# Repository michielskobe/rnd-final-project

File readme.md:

# The Blendinator

This project was made for the `Research and Development: Embedded` course of the master in engineering technology at GroupT KUL. The Blendinator is a digital mixing desk which is able to mix an analog input together with a Bluetooth input. It also features several audio effects such as echo, equalizer, volume control, etc. The full audio pipeline is implemented in VHDL and deployed on the FPGA fabric of a Xilinx device. Bluetooth connection, pipeline control and the Graphical user interface are implemented on the SoC. Details about the implementation can be found below. 

## Extra information: 
Find the docs on [Gitlab pages](https://rnd-final-project-c5cfa9.gitlab.io/).

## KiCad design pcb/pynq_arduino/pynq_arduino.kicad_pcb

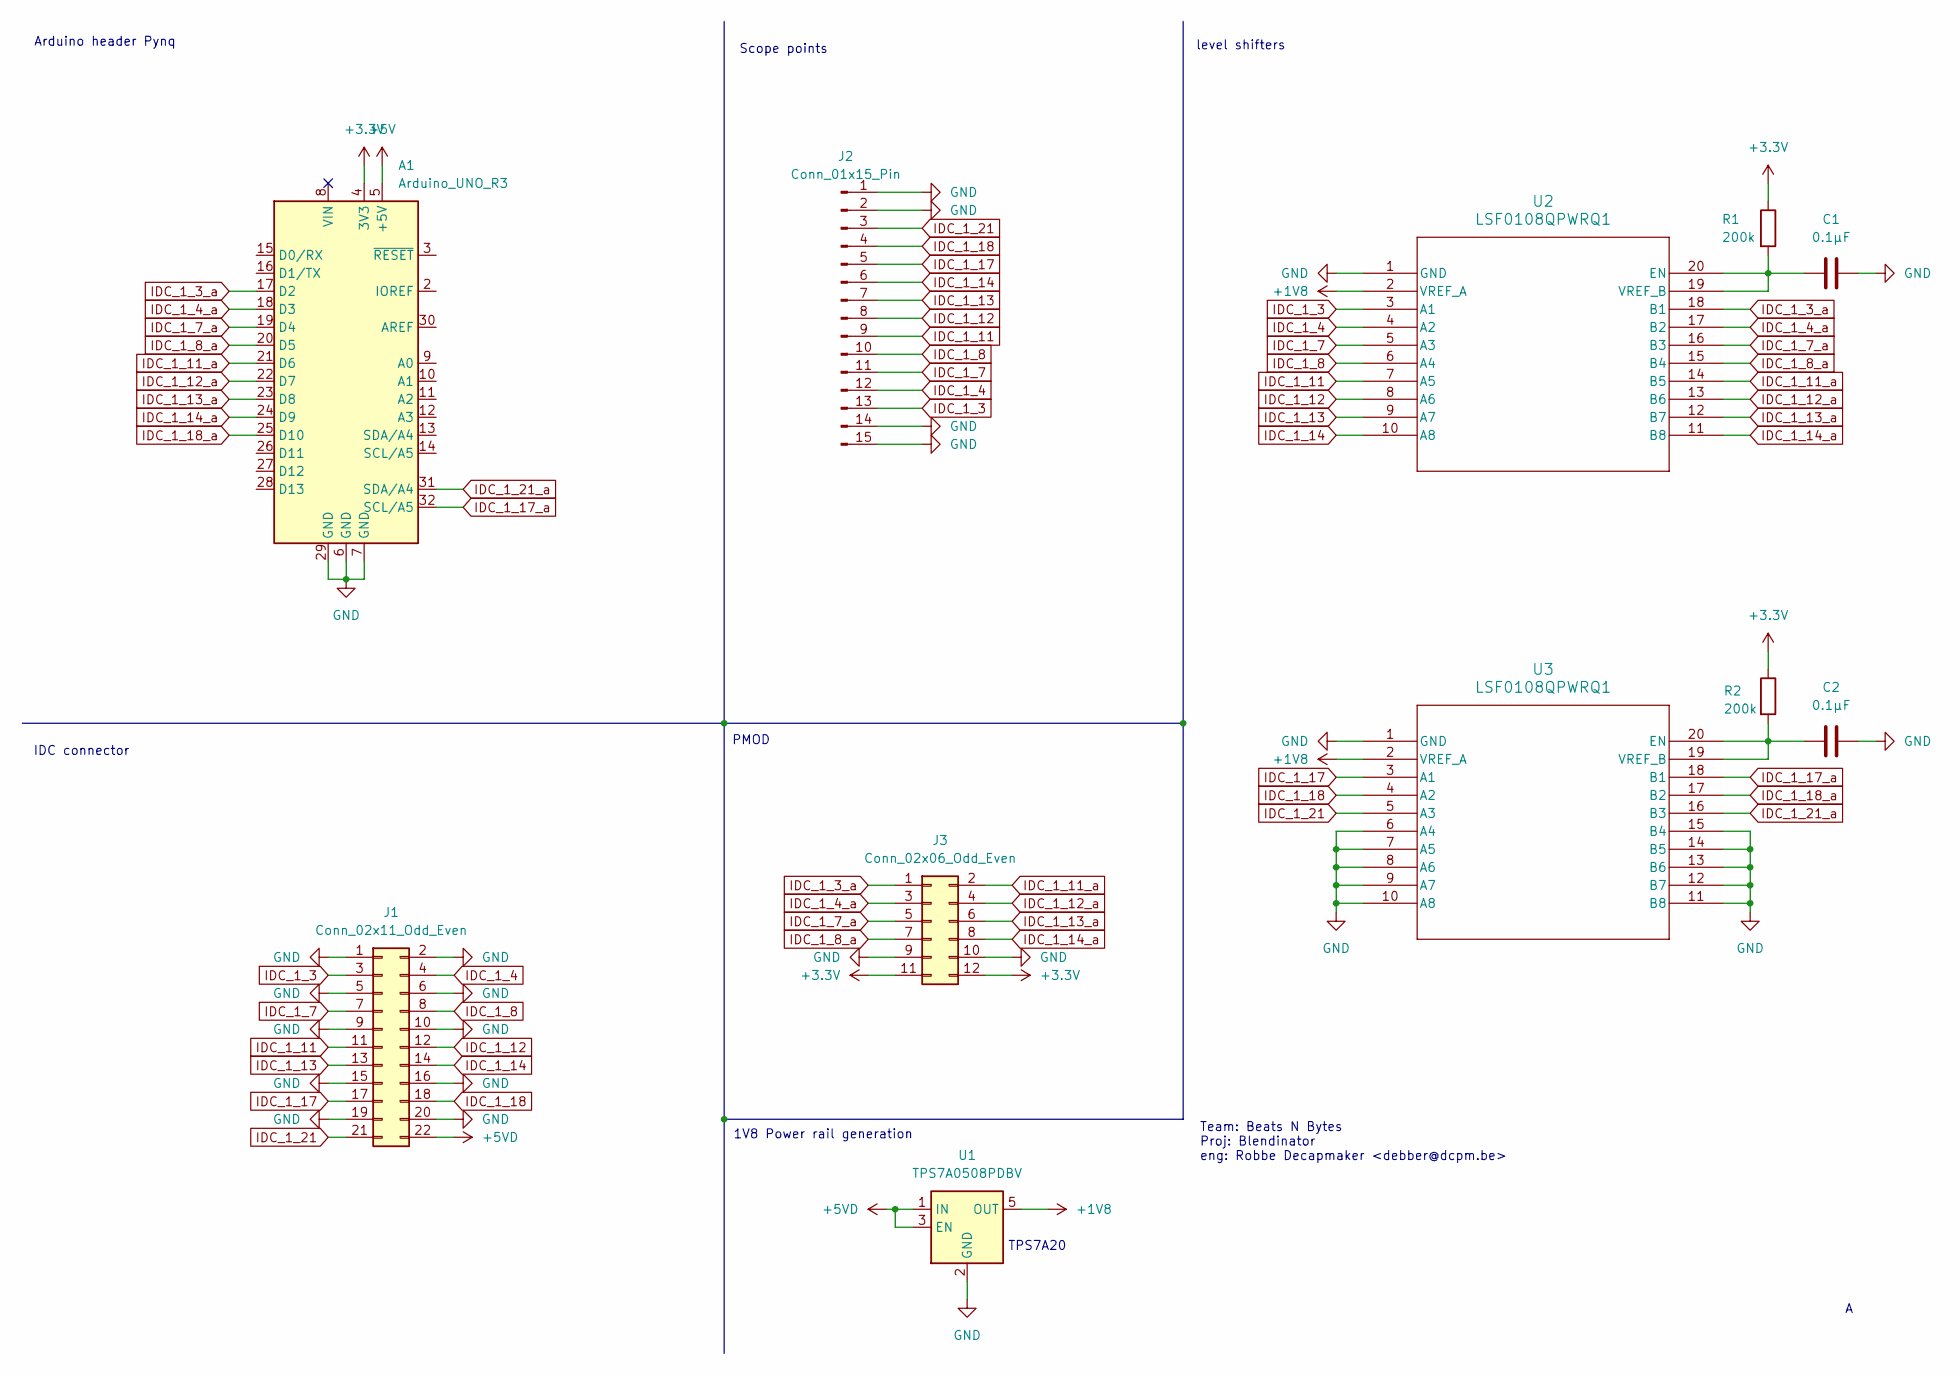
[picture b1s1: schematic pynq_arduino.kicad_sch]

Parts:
A1: Arduino_UNO_R3
C1, C2: 0.1µF; C_0805_2012Metric_Pad1.18x1.45mm_HandSolder
J1: Conn_02x11_Odd_Even; IDC-Header_2x11_P2.54mm_Vertical
J2: Conn_01x15_Pin; PinHeader_1x15_P2.54mm_Vertical
J3: Conn_02x06_Odd_Even; PinHeader_2x06_P2.54mm_Horizontal
R1, R2: 200k; R_0805_2012Metric_Pad1.20x1.40mm_HandSolder
U1: TPS7A0508PDBV; SOT-23-5
U2, U3: LSF0108QPWRQ1; PW20_TEX

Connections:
+1V8: U1.5 (OUT), U2.2 (VREF_A), U3.2 (VREF_A)
+3.3V: A1.4 (3V3), J3.11, J3.12, R1.1, R2.1
+5V: A1.5 (+5V)
+5VD: J1.22, U1.1 (IN), U1.3 (EN)
GND: A1.6 (GND), A1.7 (GND), A1.29 (GND), C1.1, C2.1, J1.1, J1.2, J1.5, J1.6, J1.9, J1.10, J1.15, J1.16, J1.19, J1.20, J2.1, J2.2, J2.14, J2.15, J3.9, J3.10, U1.2 (GND), U2.1 (GND), U3.1 (GND), U3.6 (A4), U3.7 (A5), U3.8 (A6), U3.9 (A7), U3.10 (A8), U3.11 (B8), U3.12 (B7), U3.13 (B6), U3.14 (B5), U3.15 (B4)
IDC_1_3: J1.3, J2.13, U2.3 (A1)
IDC_1_3_a: A1.17 (D2), J3.1, U2.18 (B1)
IDC_1_4: J1.4, J2.12, U2.4 (A2)
IDC_1_4_a: A1.18 (D3), J3.3, U2.17 (B2)
IDC_1_7: J1.7, J2.11, U2.5 (A3)
IDC_1_7_a: A1.19 (D4), J3.5, U2.16 (B3)
IDC_1_8: J1.8, J2.10, U2.6 (A4)
IDC_1_8_a: A1.20 (D5), J3.7, U2.15 (B4)
IDC_1_11: J1.11, J2.9, U2.7 (A5)
IDC_1_11_a: A1.21 (D6), J3.2, U2.14 (B5)
IDC_1_12: J1.12, J2.8, U2.8 (A6)
IDC_1_12_a: A1.22 (D7), J3.4, U2.13 (B6)
IDC_1_13: J1.13, J2.7, U2.9 (A7)
IDC_1_13_a: A1.23 (D8), J3.6, U2.12 (B7)
IDC_1_14: J1.14, J2.6, U2.10 (A8)
IDC_1_14_a: A1.24 (D9), J3.8, U2.11 (B8)
IDC_1_17: J1.17, J2.5, U3.3 (A1)
IDC_1_17_a: A1.32 (SCL/A5), U3.18 (B1)
IDC_1_18: J1.18, J2.4, U3.4 (A2)
IDC_1_18_a: A1.25 (D10), U3.17 (B2)
IDC_1_21: J1.21, J2.3, U3.5 (A3)
IDC_1_21_a: A1.31 (SDA/A4), U3.16 (B3)
unnamed: C1.2, R1.2, U2.19 (VREF_B), U2.20 (EN)
unnamed: C2.2, R2.2, U3.19 (VREF_B), U3.20 (EN)

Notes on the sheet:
level shifters
1V8 Power rail generation
PMOD
Scope points
TPS7A20
Arduino header Pynq
IDC connector
Team: Beats N Bytes Proj: Blendinator eng: Robbe Decapmaker <debber@dcpm.be>

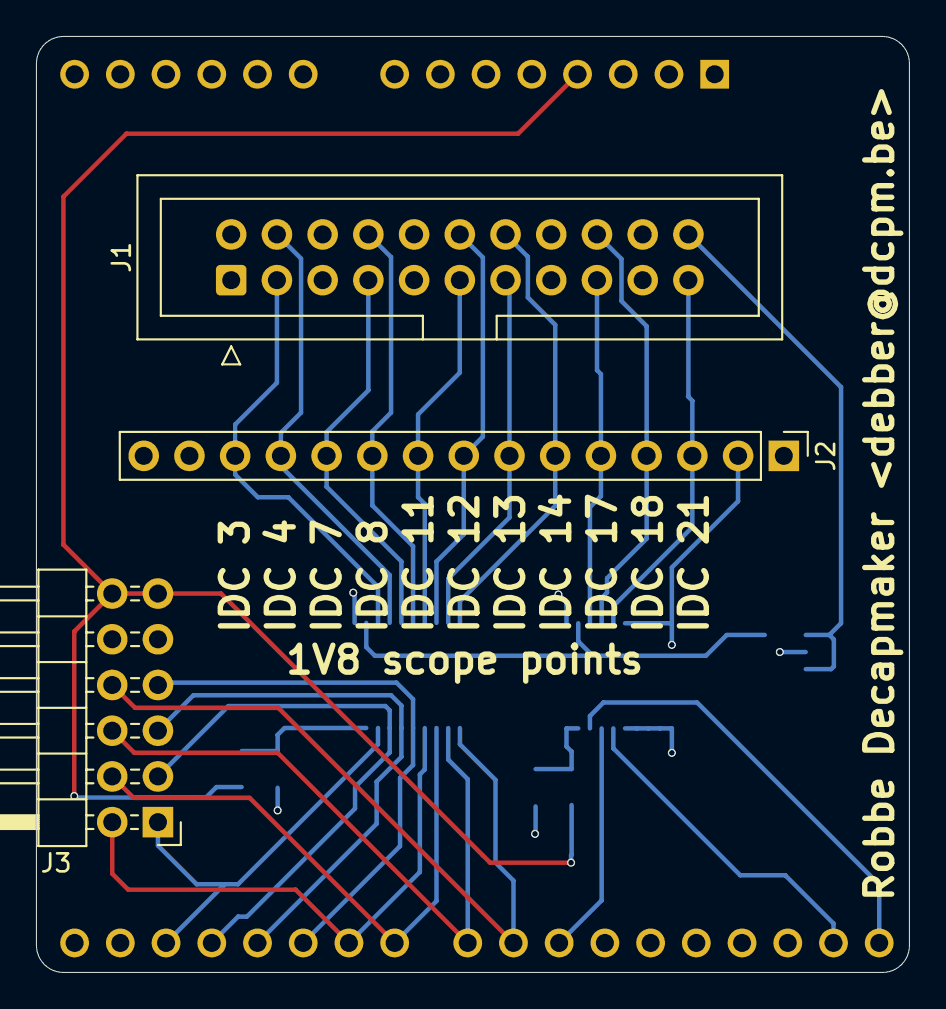
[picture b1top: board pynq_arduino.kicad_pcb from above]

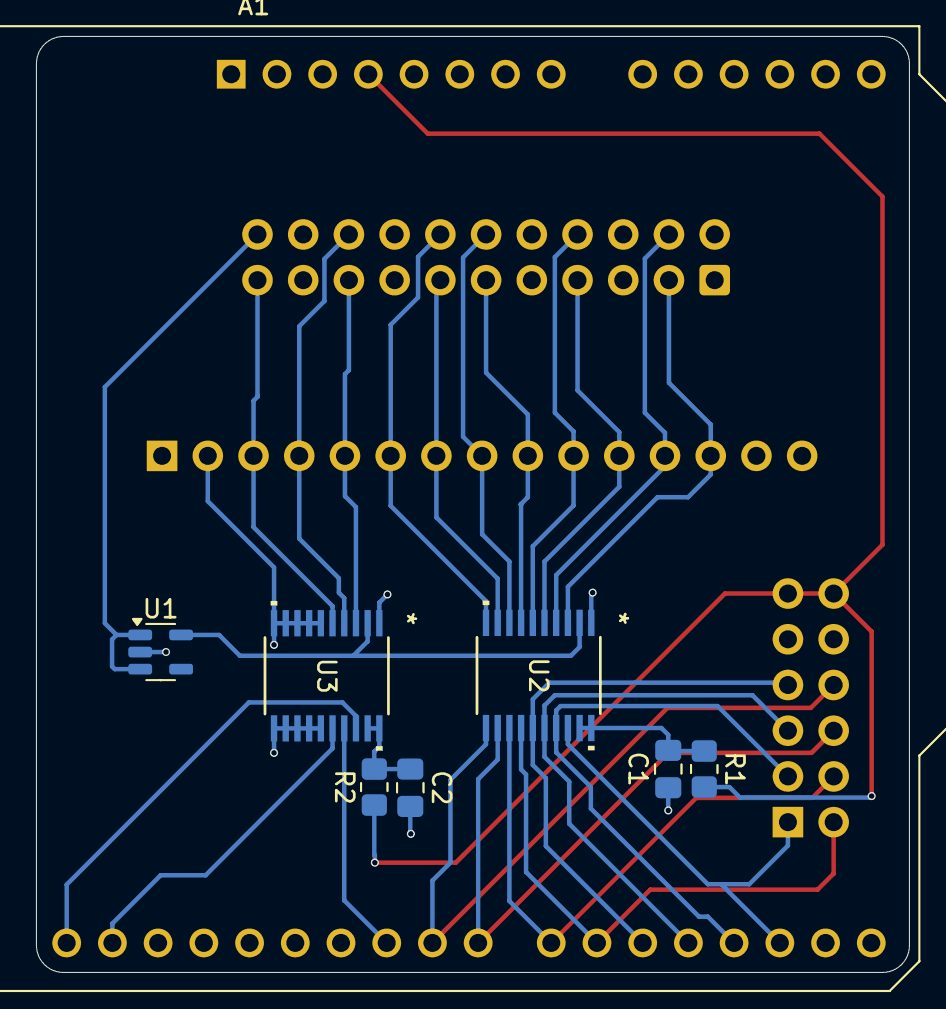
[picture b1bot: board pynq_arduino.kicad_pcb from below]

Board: 4 copper layers, 48.5 x 52.0 mm, 11 parts (8 on the bottom side), 28 nets.

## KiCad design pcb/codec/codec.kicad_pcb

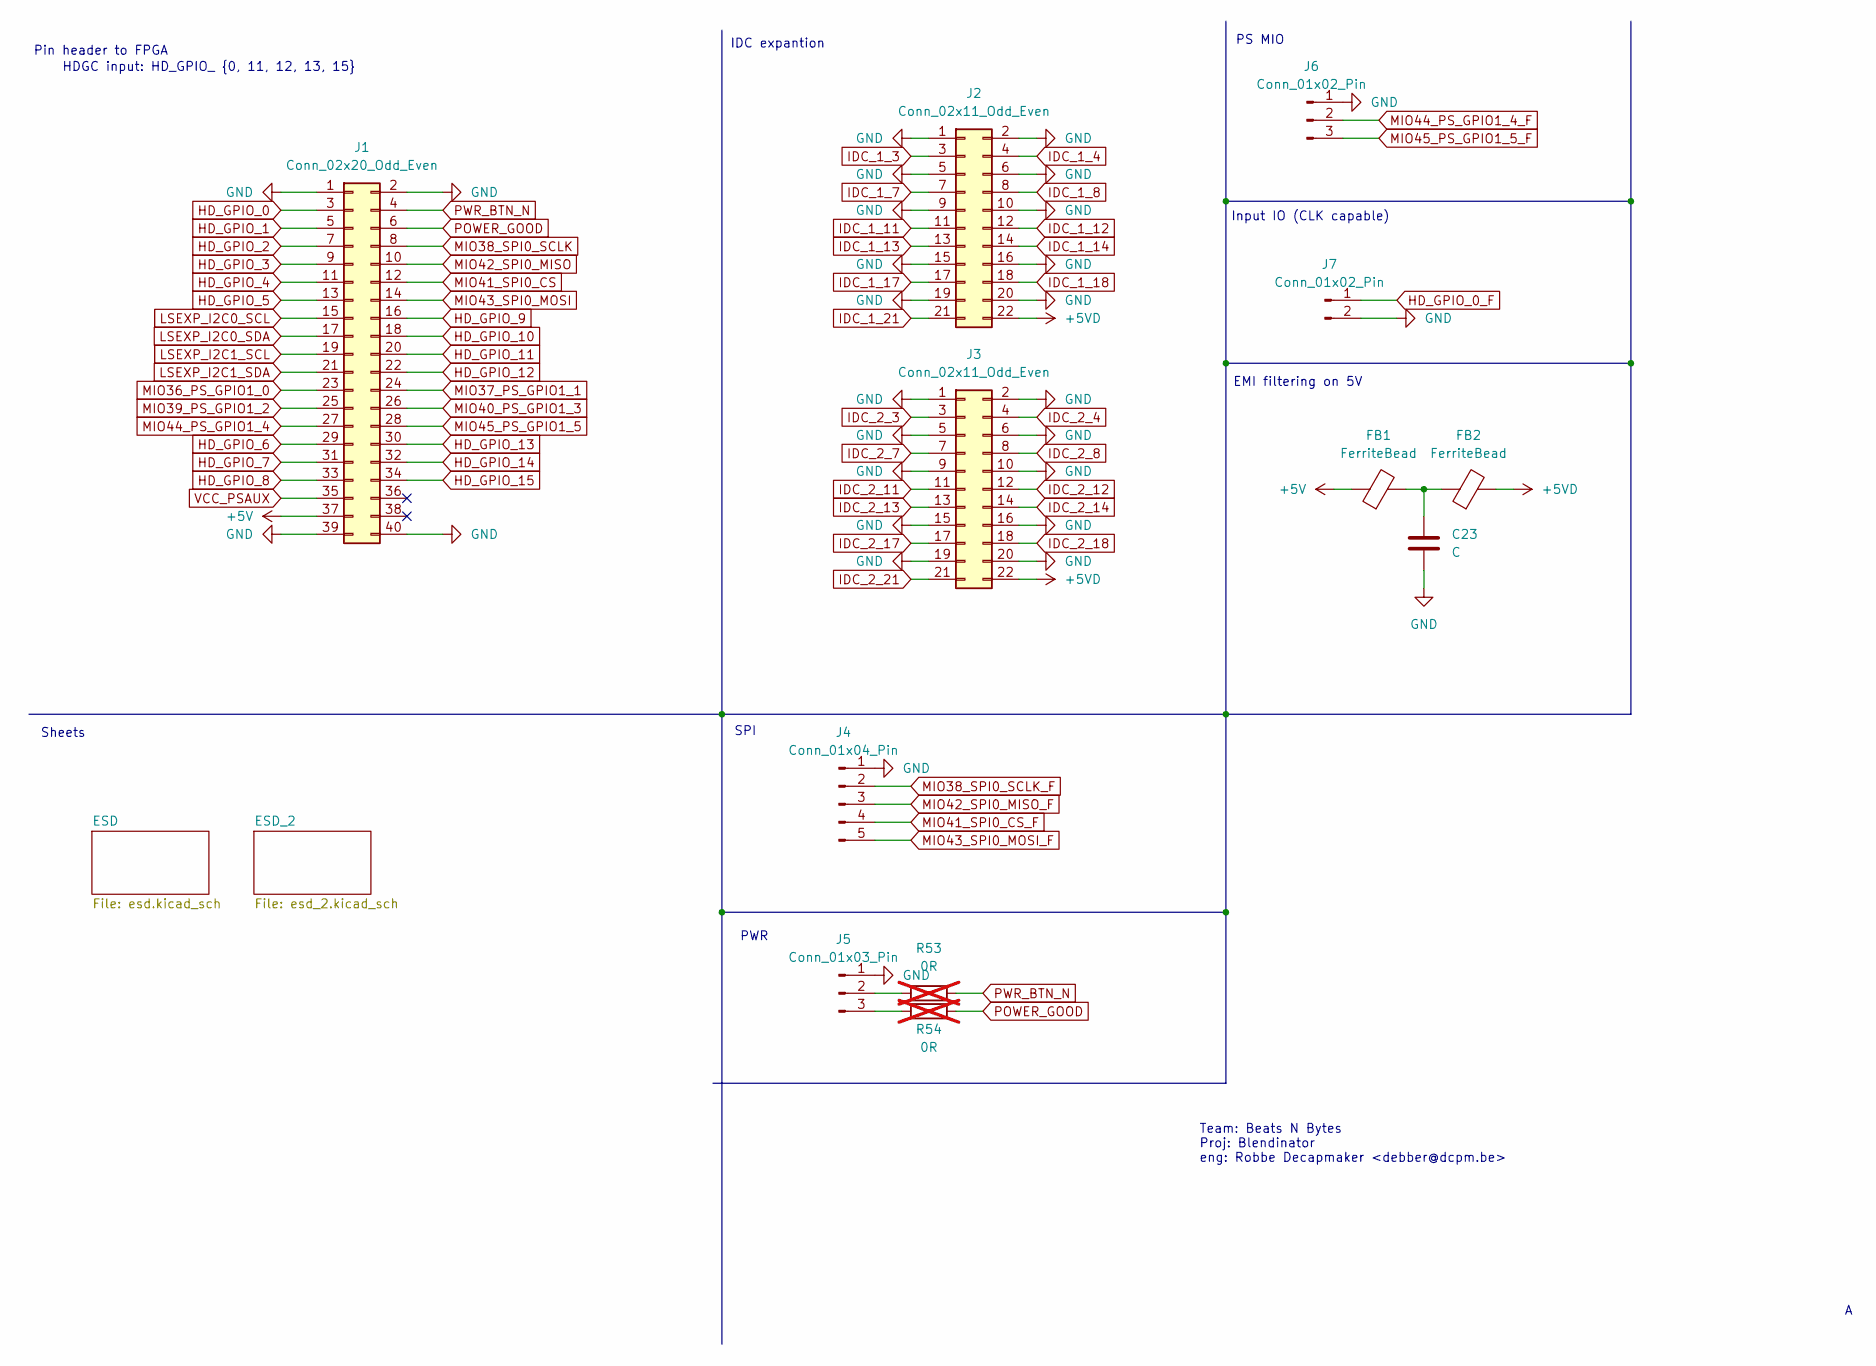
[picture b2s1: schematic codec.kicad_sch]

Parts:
C23: C; C_0805_2012Metric_Pad1.18x1.45mm_HandSolder
FB1, FB2: FerriteBead; L_0805_2012Metric_Pad1.05x1.20mm_HandSolder
J1: Conn_02x20_Odd_Even; PinHeader_2x20_P2.00mm_Vertical
J2, J3: Conn_02x11_Odd_Even; IDC-Header_2x11_P2.54mm_Vertical
J4: Conn_01x04_Pin; PinHeader_1x05_P2.54mm_Vertical
J5: Conn_01x03_Pin; PinHeader_1x03_P2.54mm_Vertical
J6: Conn_01x02_Pin; PinHeader_1x03_P2.54mm_Vertical
J7: Conn_01x02_Pin; PinHeader_1x02_P2.54mm_Vertical
R53, R54: 0R; R_0805_2012Metric_Pad1.20x1.40mm_HandSolder; not fitted

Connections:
+5V: FB1.1, J1.37
+5VD: FB2.2, J2.22, J3.22
GND: C23.2, J1.1, J1.2, J1.39, J1.40, J2.1, J2.2, J2.5, J2.6, J2.9, J2.10, J2.15, J2.16, J2.19, J2.20, J3.1, J3.2, J3.5, J3.6, J3.9, J3.10, J3.15, J3.16, J3.19, J3.20, J4.1, J5.1, J6.1, J7.2; also elsewhere on the board
HD_GPIO_0: J1.3
HD_GPIO_0_F: J7.1; also elsewhere on the board
HD_GPIO_1: J1.5; also elsewhere on the board
HD_GPIO_2: J1.7; also elsewhere on the board
HD_GPIO_3: J1.9; also elsewhere on the board
HD_GPIO_4: J1.11; also elsewhere on the board
HD_GPIO_5: J1.13; also elsewhere on the board
HD_GPIO_6: J1.29; also elsewhere on the board
HD_GPIO_7: J1.31; also elsewhere on the board
HD_GPIO_8: J1.33; also elsewhere on the board
HD_GPIO_9: J1.16; also elsewhere on the board
HD_GPIO_10: J1.18; also elsewhere on the board
HD_GPIO_11: J1.20; also elsewhere on the board
HD_GPIO_12: J1.22; also elsewhere on the board
HD_GPIO_13: J1.30; also elsewhere on the board
HD_GPIO_14: J1.32; also elsewhere on the board
HD_GPIO_15: J1.34; also elsewhere on the board
IDC_1_3: J2.3; also elsewhere on the board
IDC_1_4: J2.4; also elsewhere on the board
IDC_1_7: J2.7; also elsewhere on the board
IDC_1_8: J2.8; also elsewhere on the board
IDC_1_11: J2.11; also elsewhere on the board
IDC_1_12: J2.12; also elsewhere on the board
IDC_1_13: J2.13; also elsewhere on the board
IDC_1_14: J2.14; also elsewhere on the board
IDC_1_17: J2.17; also elsewhere on the board
IDC_1_18: J2.18; also elsewhere on the board
IDC_1_21: J2.21; also elsewhere on the board
IDC_2_3: J3.3; also elsewhere on the board
IDC_2_4: J3.4; also elsewhere on the board
IDC_2_7: J3.7; also elsewhere on the board
IDC_2_8: J3.8; also elsewhere on the board
IDC_2_11: J3.11; also elsewhere on the board
IDC_2_12: J3.12; also elsewhere on the board
IDC_2_13: J3.13; also elsewhere on the board
IDC_2_14: J3.14; also elsewhere on the board
IDC_2_17: J3.17; also elsewhere on the board
IDC_2_18: J3.18; also elsewhere on the board
IDC_2_21: J3.21; also elsewhere on the board
LSEXP_I2C0_SCL: J1.15; also elsewhere on the board
LSEXP_I2C0_SDA: J1.17; also elsewhere on the board
LSEXP_I2C1_SCL: J1.19; also elsewhere on the board
LSEXP_I2C1_SDA: J1.21; also elsewhere on the board
MIO36_PS_GPIO1_0: J1.23; also elsewhere on the board
MIO37_PS_GPIO1_1: J1.24; also elsewhere on the board
MIO38_SPI0_SCLK: J1.8; also elsewhere on the board
MIO38_SPI0_SCLK_F: J4.2; also elsewhere on the board
MIO39_PS_GPIO1_2: J1.25; also elsewhere on the board
MIO40_PS_GPIO1_3: J1.26; also elsewhere on the board
MIO41_SPI0_CS: J1.12; also elsewhere on the board
MIO41_SPI0_CS_F: J4.4; also elsewhere on the board
MIO42_SPI0_MISO: J1.10; also elsewhere on the board
MIO42_SPI0_MISO_F: J4.3; also elsewhere on the board
MIO43_SPI0_MOSI: J1.14; also elsewhere on the board
MIO43_SPI0_MOSI_F: J4.5; also elsewhere on the board
MIO44_PS_GPIO1_4: J1.27; also elsewhere on the board
MIO44_PS_GPIO1_4_F: J6.2; also elsewhere on the board
MIO45_PS_GPIO1_5: J1.28; also elsewhere on the board
MIO45_PS_GPIO1_5_F: J6.3; also elsewhere on the board
unnamed: C23.1, FB1.2, FB2.1
unnamed: J5.2, R53.1
unnamed: J5.3, R54.1
POWER_GOOD: J1.6, R54.2
PWR_BTN_N: J1.4, R53.2
VCC_PSAUX: J1.35

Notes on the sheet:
Team: Beats N Bytes Proj: Blendinator eng: Robbe Decapmaker <debber@dcpm.be>
Input IO (CLK capable)
EMI filtering on 5V
Sheets
HDGC input: HD_GPIO_ {0, 11, 12, 13, 15}
PS MIO
IDC expantion
PWR
Pin header to FPGA
SPI

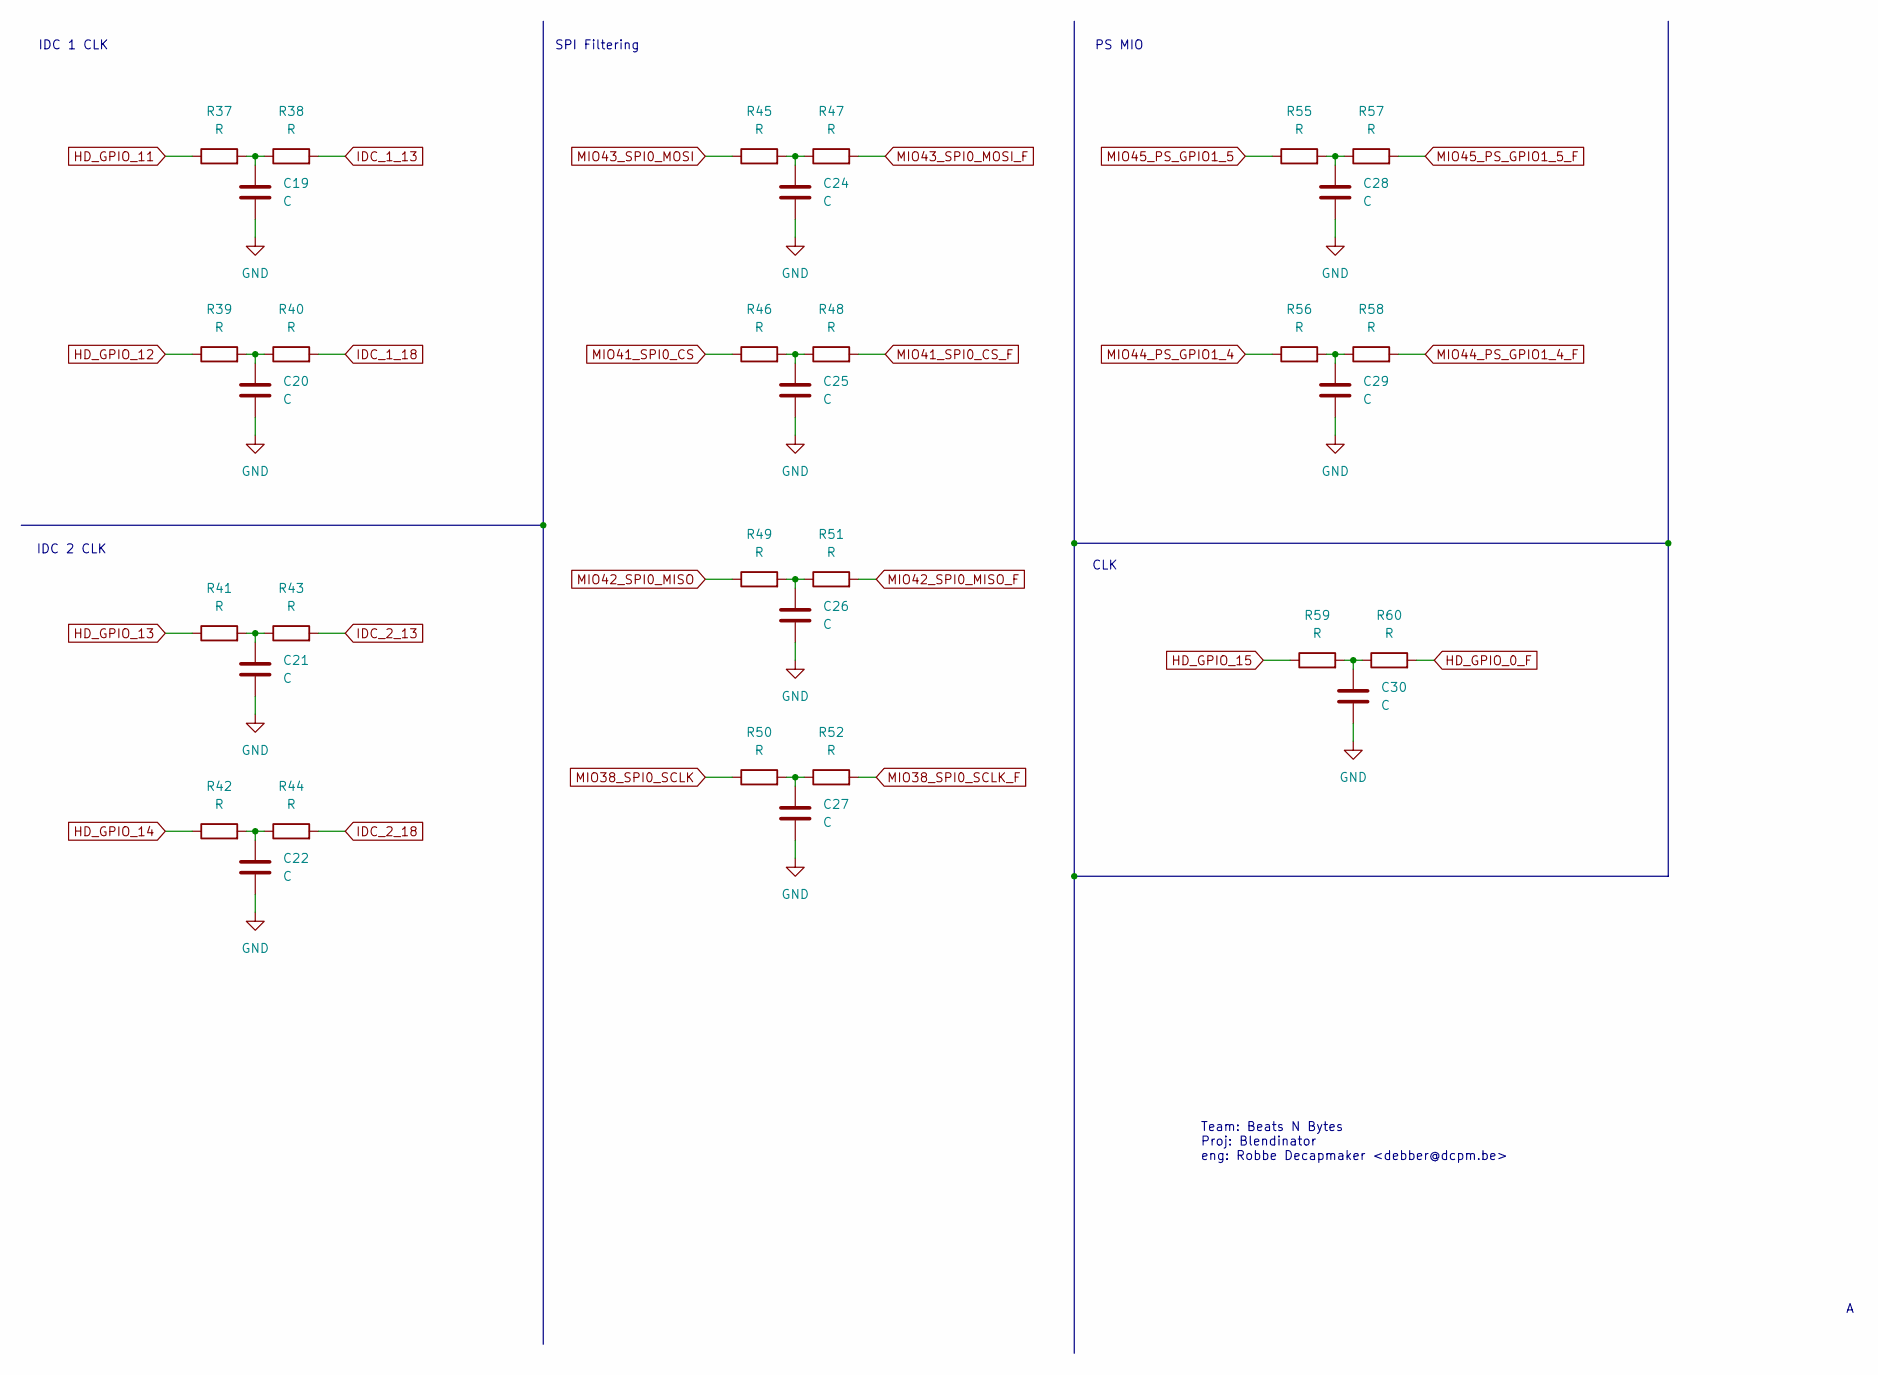
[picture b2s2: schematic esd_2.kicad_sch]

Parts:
C19, C20, C21, C22, C24, C25, C26, C27, C28, C29, C30: C; C_0805_2012Metric_Pad1.18x1.45mm_HandSolder
R37, R38, R39, R40, R41, R42, R43, R44, R45, R46, R47, R48, R49, R50, R51, R52, R55, R56, R57, R58, R59, R60: R; R_0805_2012Metric_Pad1.20x1.40mm_HandSolder

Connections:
GND: C19.2, C20.2, C21.2, C22.2, C24.2, C25.2, C26.2, C27.2, C28.2, C29.2, C30.2; also elsewhere on the board
HD_GPIO_0_F: R60.2; also elsewhere on the board
HD_GPIO_11: R37.1; also elsewhere on the board
HD_GPIO_12: R39.1; also elsewhere on the board
HD_GPIO_13: R41.1; also elsewhere on the board
HD_GPIO_14: R42.1; also elsewhere on the board
HD_GPIO_15: R59.1; also elsewhere on the board
IDC_1_13: R38.2; also elsewhere on the board
IDC_1_18: R40.2; also elsewhere on the board
IDC_2_13: R43.2; also elsewhere on the board
IDC_2_18: R44.2; also elsewhere on the board
MIO38_SPI0_SCLK: R50.1; also elsewhere on the board
MIO38_SPI0_SCLK_F: R52.2; also elsewhere on the board
MIO41_SPI0_CS: R46.1; also elsewhere on the board
MIO41_SPI0_CS_F: R48.2; also elsewhere on the board
MIO42_SPI0_MISO: R49.1; also elsewhere on the board
MIO42_SPI0_MISO_F: R51.2; also elsewhere on the board
MIO43_SPI0_MOSI: R45.1; also elsewhere on the board
MIO43_SPI0_MOSI_F: R47.2; also elsewhere on the board
MIO44_PS_GPIO1_4: R56.1; also elsewhere on the board
MIO44_PS_GPIO1_4_F: R58.2; also elsewhere on the board
MIO45_PS_GPIO1_5: R55.1; also elsewhere on the board
MIO45_PS_GPIO1_5_F: R57.2; also elsewhere on the board
unnamed: C19.1, R37.2, R38.1
unnamed: C20.1, R39.2, R40.1
unnamed: C21.1, R41.2, R43.1
unnamed: C22.1, R42.2, R44.1
unnamed: C24.1, R45.2, R47.1
unnamed: C25.1, R46.2, R48.1
unnamed: C26.1, R49.2, R51.1
unnamed: C27.1, R50.2, R52.1
unnamed: C28.1, R55.2, R57.1
unnamed: C29.1, R56.2, R58.1
unnamed: C30.1, R59.2, R60.1

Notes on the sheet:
IDC 1 CLK
PS MIO
IDC 2 CLK
Team: Beats N Bytes Proj: Blendinator eng: Robbe Decapmaker <debber@dcpm.be>
CLK
SPI Filtering

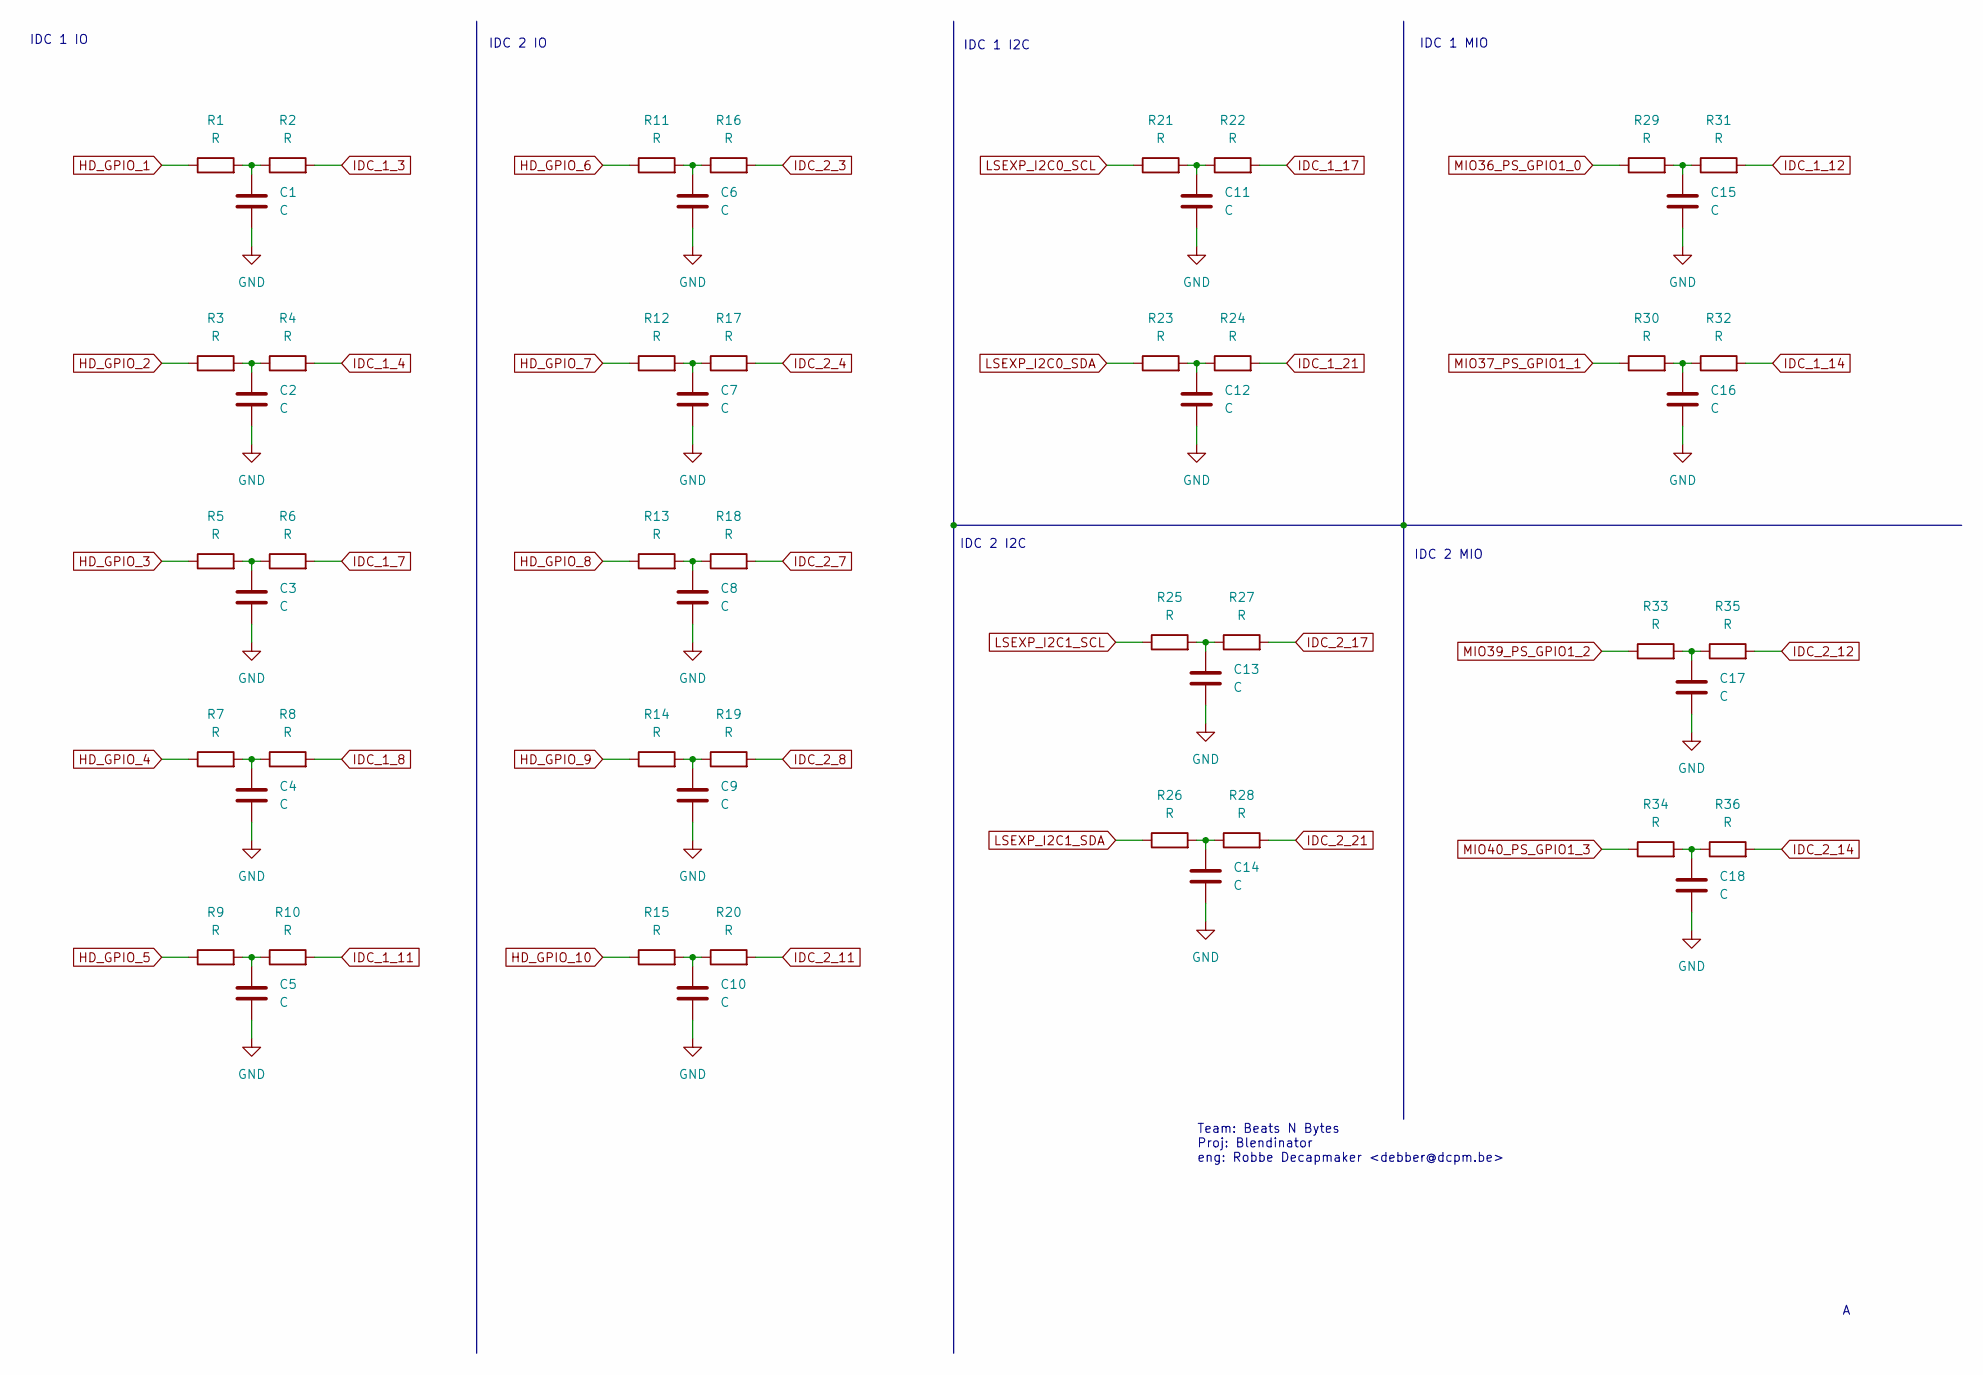
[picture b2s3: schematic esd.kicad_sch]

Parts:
C1, C2, C3, C4, C5, C6, C7, C8, C9, C10, C11, C12, C13, C14, C15, C16, C17, C18: C; C_0805_2012Metric_Pad1.18x1.45mm_HandSolder
R1, R2, R3, R4, R5, R6, R7, R8, R9, R10, R11, R12, R13, R14, R15, R16, R17, R18, R19, R20, R21, R22, R23, R24, R25, R26, R27, R28, R29, R30, R31, R32, R33, R34, R35, R36: R; R_0805_2012Metric_Pad1.20x1.40mm_HandSolder

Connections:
GND: C1.2, C2.2, C3.2, C4.2, C5.2, C6.2, C7.2, C8.2, C9.2, C10.2, C11.2, C12.2, C13.2, C14.2, C15.2, C16.2, C17.2, C18.2; also elsewhere on the board
HD_GPIO_1: R1.1; also elsewhere on the board
HD_GPIO_2: R3.1; also elsewhere on the board
HD_GPIO_3: R5.1; also elsewhere on the board
HD_GPIO_4: R7.1; also elsewhere on the board
HD_GPIO_5: R9.1; also elsewhere on the board
HD_GPIO_6: R11.1; also elsewhere on the board
HD_GPIO_7: R12.1; also elsewhere on the board
HD_GPIO_8: R13.1; also elsewhere on the board
HD_GPIO_9: R14.1; also elsewhere on the board
HD_GPIO_10: R15.1; also elsewhere on the board
IDC_1_3: R2.2; also elsewhere on the board
IDC_1_4: R4.2; also elsewhere on the board
IDC_1_7: R6.2; also elsewhere on the board
IDC_1_8: R8.2; also elsewhere on the board
IDC_1_11: R10.2; also elsewhere on the board
IDC_1_12: R31.2; also elsewhere on the board
IDC_1_14: R32.2; also elsewhere on the board
IDC_1_17: R22.2; also elsewhere on the board
IDC_1_21: R24.2; also elsewhere on the board
IDC_2_3: R16.2; also elsewhere on the board
IDC_2_4: R17.2; also elsewhere on the board
IDC_2_7: R18.2; also elsewhere on the board
IDC_2_8: R19.2; also elsewhere on the board
IDC_2_11: R20.2; also elsewhere on the board
IDC_2_12: R35.2; also elsewhere on the board
IDC_2_14: R36.2; also elsewhere on the board
IDC_2_17: R27.2; also elsewhere on the board
IDC_2_21: R28.2; also elsewhere on the board
LSEXP_I2C0_SCL: R21.1; also elsewhere on the board
LSEXP_I2C0_SDA: R23.1; also elsewhere on the board
LSEXP_I2C1_SCL: R25.1; also elsewhere on the board
LSEXP_I2C1_SDA: R26.1; also elsewhere on the board
MIO36_PS_GPIO1_0: R29.1; also elsewhere on the board
MIO37_PS_GPIO1_1: R30.1; also elsewhere on the board
MIO39_PS_GPIO1_2: R33.1; also elsewhere on the board
MIO40_PS_GPIO1_3: R34.1; also elsewhere on the board
unnamed: C1.1, R1.2, R2.1
unnamed: C2.1, R3.2, R4.1
unnamed: C3.1, R5.2, R6.1
unnamed: C4.1, R7.2, R8.1
unnamed: C5.1, R9.2, R10.1
unnamed: C6.1, R11.2, R16.1
unnamed: C7.1, R12.2, R17.1
unnamed: C8.1, R13.2, R18.1
unnamed: C9.1, R14.2, R19.1
unnamed: C10.1, R15.2, R20.1
unnamed: C11.1, R21.2, R22.1
unnamed: C12.1, R23.2, R24.1
unnamed: C13.1, R25.2, R27.1
unnamed: C14.1, R26.2, R28.1
unnamed: C15.1, R29.2, R31.1
unnamed: C16.1, R30.2, R32.1
unnamed: C17.1, R33.2, R35.1
unnamed: C18.1, R34.2, R36.1

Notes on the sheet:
IDC 2 IO
IDC 1 IO
IDC 1 I2C
IDC 2 MIO
IDC 1 MIO
Team: Beats N Bytes Proj: Blendinator eng: Robbe Decapmaker <debber@dcpm.be>
IDC 2 I2C

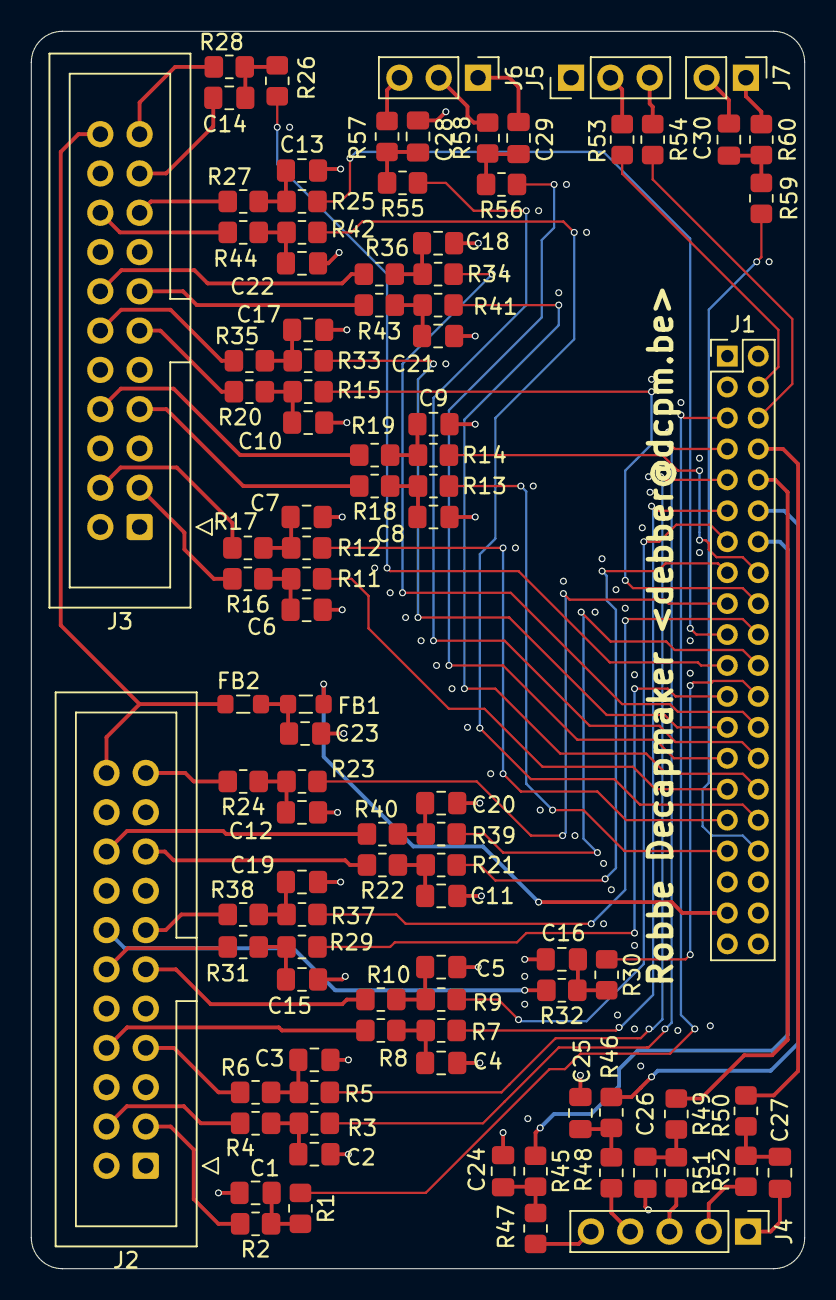
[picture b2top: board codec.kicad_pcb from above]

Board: 4 copper layers, 50.0 x 80.0 mm, 99 parts (0 on the bottom side), 95 nets.

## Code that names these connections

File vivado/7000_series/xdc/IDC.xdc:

#######################################################################################################################
# RND IDC interconnect constraint file for TUL PYNQ-Z2
# Eng: Robbe Decapmaker <debber@dcpm.be>
# Date: 24-10-2024
#
# This file describes the constraints needed to use the IDC pcb's properly on the PYNQ-Z2 board.
#
# Pin comment format: $IDC_PIN ultra $ULTRA_SCHEMATIC_PIN <==> $PYNQ_SCHEMATIC_PIN pynq
#######################################################################################################################

####################
# IDC connector description
####################
# IDC_3 ultra HD_GPIO_1 <==> ar_2 pynq
#set_property -dict { PACKAGE_PIN U13   IOSTANDARD LVCMOS33 } [get_ports { ar[2] }]; #IO_L3P_T0_DQS_PUDC_B_34 Sch=ar[2]
# IDC_4 ultra HD_GPIO_2 <==> ar_3 pynq
#set_property -dict { PACKAGE_PIN V13   IOSTANDARD LVCMOS33 } [get_ports { ar[3] }]; #IO_L3N_T0_DQS_34 Sch=ar[3]
# IDC_7 ultra HD_GPIO_3 <==> ar_4 pynq
#set_property -dict { PACKAGE_PIN V15   IOSTANDARD LVCMOS33 } [get_ports { ar[4] }]; #IO_L10P_T1_34 Sch=ar[4]
# IDC_8 ultra HD_GPIO_4 <==> ar_5 pynq
#set_property -dict { PACKAGE_PIN T15   IOSTANDARD LVCMOS33 } [get_ports { ar[5] }]; #IO_L5N_T0_34 Sch=ar[5]
# IDC_11 ultra HD_GPIO_5 <==> ar_6 pynq
#set_property -dict { PACKAGE_PIN R16   IOSTANDARD LVCMOS33 } [get_ports { ar[6] }]; #IO_L19P_T3_34 Sch=ar[6]
# IDC_12 ultra MIO36_PS_GPIO1_0 <==> ar_7 pynq
#set_property -dict { PACKAGE_PIN U17   IOSTANDARD LVCMOS33 } [get_ports { ar[7] }]; #IO_L9N_T1_DQS_34 Sch=ar[7]
# IDC_13 ultra HD_GPIO_11 (clk ultra input) <==> ar_8 pynq
#set_property -dict { PACKAGE_PIN V17   IOSTANDARD LVCMOS33 } [get_ports { ar[8] }]; #IO_L21P_T3_DQS_34 Sch=ar[8]
# IDC_14 ultra MIO37_PS_GPIO1_1 <==> ar_9 pynq
#set_property -dict { PACKAGE_PIN V18   IOSTANDARD LVCMOS33 } [get_ports { ar[9] }]; #IO_L21N_T3_DQS_34 Sch=ar[9]
# IDC_18 ultra HD_GPIO_12 (clk ultra input) <==> ar_10 pynq
#set_property -dict { PACKAGE_PIN T16   IOSTANDARD LVCMOS33 } [get_ports { ar[10] }]; #IO_L9P_T1_DQS_34 Sch=ar[10]

# I2C IDC
# IDC_17 ultra I2C_SCL <==> ar_scl pynq
#set_property -dict { PACKAGE_PIN P16   IOSTANDARD LVCMOS33 } [get_ports { ar_scl }]; #IO_L24N_T3_34 Sch=ar_scl
# IDC_21 ultra I2C_SDA <==> ar_scl pynq
#set_property -dict { PACKAGE_PIN P15   IOSTANDARD LVCMOS33 } [get_ports { ar_sda }]; #IO_L24P_T3_34 Sch=ar_sda


####################
# Not part of the IDC but present on the PCB
####################
#set_property -dict { PACKAGE_PIN T14   IOSTANDARD LVCMOS33 } [get_ports { ar[0] }]; #IO_L5P_T0_34 Sch=ar[0]
#set_property -dict { PACKAGE_PIN U12   IOSTANDARD LVCMOS33 } [get_ports { ar[1] }]; #IO_L2N_T0_34 Sch=ar[1]
#set_property -dict { PACKAGE_PIN R17   IOSTANDARD LVCMOS33 } [get_ports { ar[11] }]; #IO_L19N_T3_VREF_34 Sch=ar[11]
#set_property -dict { PACKAGE_PIN P18   IOSTANDARD LVCMOS33 } [get_ports { ar[12] }]; #IO_L23N_T3_34 Sch=ar[12]
#set_property -dict { PACKAGE_PIN N17   IOSTANDARD LVCMOS33 } [get_ports { ar[13] }]; #IO_L23P_T3_34 Sch=ar[13]
#set_property -dict { PACKAGE_PIN Y13   IOSTANDARD LVCMOS33 } [get_ports { a }]; #IO_L20N_T3_13 Sch=a

##Arduino Digital I/O On Outer Analog Header
##NOTE: These pins should be used when using the analog header signals A0-A5 as digital I/O

#set_property -dict { PACKAGE_PIN Y11   IOSTANDARD LVCMOS33 } [get_ports { a[0] }]; #IO_L18N_T2_13 Sch=a[0]
#set_property -dict { PACKAGE_PIN Y12   IOSTANDARD LVCMOS33 } [get_ports { a[1] }]; #IO_L20P_T3_13 Sch=a[1]
#set_property -dict { PACKAGE_PIN W11   IOSTANDARD LVCMOS33 } [get_ports { a[2] }]; #IO_L18P_T2_13 Sch=a[2]
#set_property -dict { PACKAGE_PIN V11   IOSTANDARD LVCMOS33 } [get_ports { a[3] }]; #IO_L21P_T3_DQS_13 Sch=a[3]
#set_property -dict { PACKAGE_PIN T5    IOSTANDARD LVCMOS33 } [get_ports { a[4] }]; #IO_L19P_T3_13 Sch=a[4]
#set_property -dict { PACKAGE_PIN U10   IOSTANDARD LVCMOS33 } [get_ports { a[5] }]; #IO_L12N_T1_MRCC_13 Sch=a[5]
